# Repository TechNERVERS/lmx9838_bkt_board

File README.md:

# lmx9838_bkt_board
A Breakout board for TI LMX9838 Bluetooth Module made in Autodesk EAGLE 

This is a rev 1.0 of the module. It includes all the pin breakouts and a usb connector for powering the board. 

Attached are the gerbers of the board for easy manufacturing 

[TO DOs]
1. Include a USB to serial in the next iteration of the board 

P.S> I will update the pdf subsequentily

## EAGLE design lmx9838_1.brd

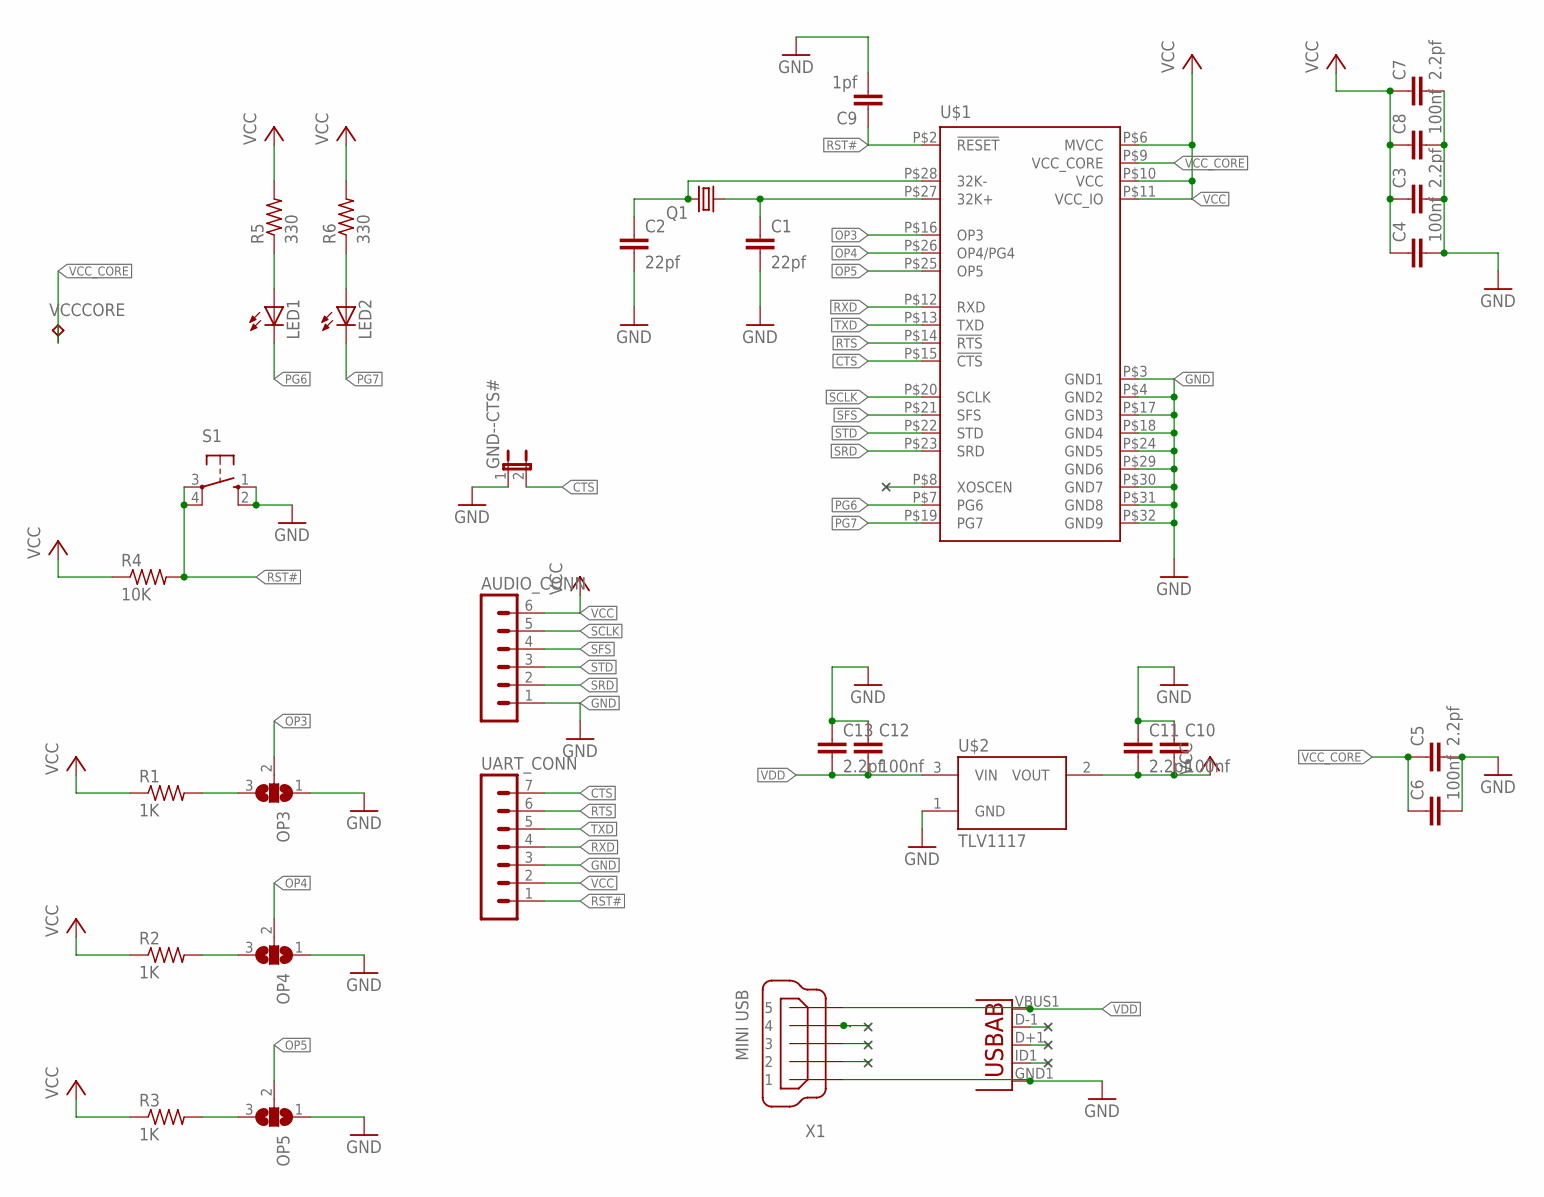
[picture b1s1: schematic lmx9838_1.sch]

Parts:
AUDIO_CONN: MA06-1
C1, C2: 22pf; C0805K
C3, C5, C7, C11, C13: 2.2pf; C0805K
C4, C6, C8, C10, C12: 100nf; C0805K
C9: 1pf; C0805K
GND--CTS#: JP1E; JP1
LED1, LED2: LEDCHIPLED_0805; CHIPLED_0805
OP3, OP4, OP5: SJ2W; SJ_2
Q1: CRYSTALTC26H; TC26H
R1, R2, R3: 1K; R0805
R4: 10K; R0805
R5, R6: 330; R0805
S1: 10-XX; B3F-10XX
U1: USB""; USB-MICRO-SMD
U$1: LMX9838; LTCC70
U$2: TLV1117; SOT223
UART_CONN: MA07-1
VCCCORE: TPB1,27; B1,27
X1: MINI USB; UX60-MB-5ST

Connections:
CTS: GND--CTS#.2, U$1.P$15 (!CTS), UART_CONN.7
GND: AUDIO_CONN.1, C1.2, C2.2, C3.2, C4.2, C5.2, C6.2, C7.2, C8.2, C9.2, C10.1, C11.1, C12.1, C13.1, GND--CTS#.1, OP3.1, OP4.1, OP5.1, S1.1 (S), S1.2 (S1), U1.GND1 (GND), U$1.P$3 (GND1), U$1.P$4 (GND2), U$1.P$17 (GND3), U$1.P$18 (GND4), U$1.P$24 (GND5), U$1.P$29 (GND6), U$1.P$30 (GND7), U$1.P$31 (GND8), U$1.P$32 (GND9), U$2.1 (GND), UART_CONN.3, X1.1
unnamed: OP3.3, R1.2
unnamed: OP4.3, R2.2
unnamed: OP5.3, R3.2
unnamed: LED1.A, R5.1
unnamed: C2.1, Q1.2, U$1.P$28 (32K-)
unnamed: C1.1, Q1.1, U$1.P$27 (32K+)
unnamed: LED2.A, R6.1
OP3: OP3.2, U$1.P$16 (OP3)
OP4: OP4.2, U$1.P$26 (OP4/PG4)
OP5: OP5.2, U$1.P$25 (OP5)
PG6: LED1.C, U$1.P$7 (PG6)
PG7: LED2.C, U$1.P$19 (PG7)
RST#: C9.1, R4.2, S1.3, S1.4 (P1), U$1.P$2 (!RESET), UART_CONN.1
RTS: U$1.P$14 (!RTS), UART_CONN.6
RXD: U$1.P$12 (RXD), UART_CONN.4
SCLK: AUDIO_CONN.5, U$1.P$20 (SCLK)
SFS: AUDIO_CONN.4, U$1.P$21 (SFS)
SRD: AUDIO_CONN.2, U$1.P$23 (SRD)
STD: AUDIO_CONN.3, U$1.P$22 (STD)
TXD: U$1.P$13 (TXD), UART_CONN.5
VCC: AUDIO_CONN.6, C3.1, C4.1, C7.1, C8.1, C10.2, C11.2, R1.1, R2.1, R3.1, R4.1, R5.2, R6.2, U$1.P$6 (MVCC), U$1.P$10 (VCC), U$1.P$11 (VCC_IO), U$2.2 (VOUT), UART_CONN.2
VCC_CORE: C5.1, C6.1, U$1.P$9 (VCC_CORE), VCCCORE.TP
VDD: C12.2, C13.2, U1.VBUS1 (VBUS), U$2.3 (VIN), X1.5
VOUT2: U$2.4 (VOUT2)

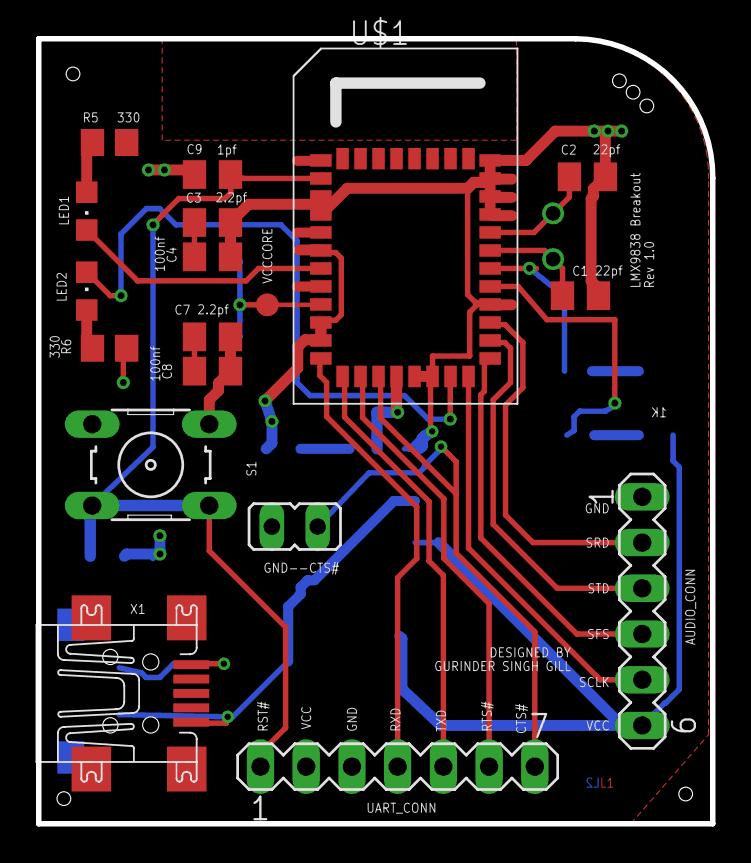
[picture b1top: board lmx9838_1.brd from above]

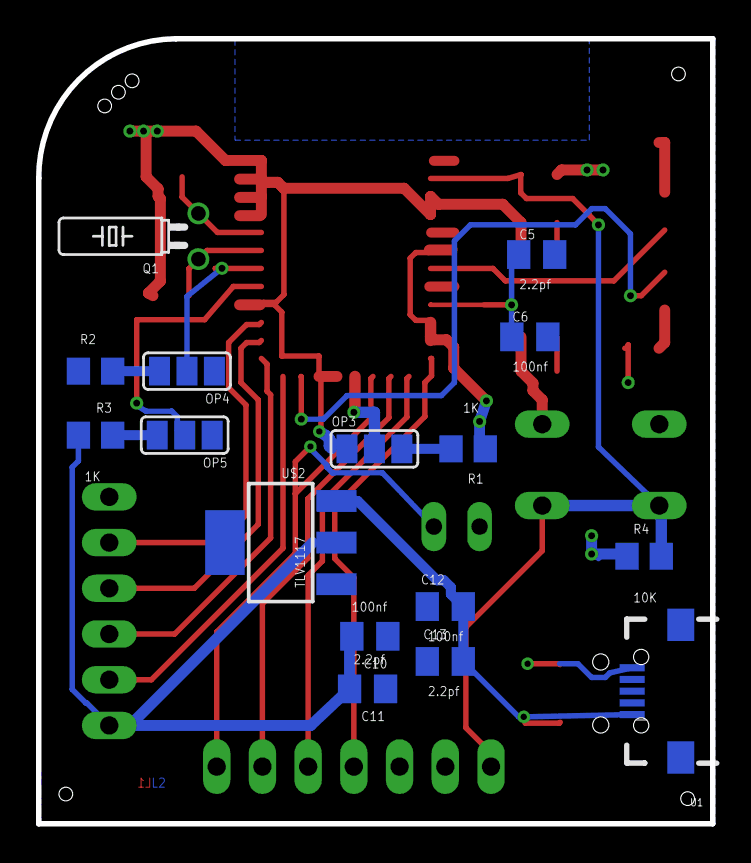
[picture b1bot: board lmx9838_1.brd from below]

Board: 2 copper layers, 37.4 x 43.6 mm, 34 parts (16 on the bottom side), 25 nets.

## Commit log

2017-08-02 REV 1.0
2017-09-08 Bug Fixes Rev 2.0
2017-09-24 added pcb images
